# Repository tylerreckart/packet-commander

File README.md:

# Packet Commander
Complete 8-button WiFi IoT controller with hardware designs, firmware, and desktop configurator. Advanced configuration management, power optimization, and multi-protocol capabilities.

## Overview

Packet Commander is a complete IoT development platform featuring 8 programmable buttons with LED feedback, comprehensive WiFi connectivity, and intelligent power management. Includes hardware schematics, ESP32 firmware, and cross-platform Electron configurator for smart home automation, network testing, and custom IoT applications.

### Key Features
- **8 Programmable Buttons**: Directly supports HTTP and Webhook actions.
- **Smart Power Management**: Includes battery monitoring and optimized CPU frequency for power efficiency.
- **Desktop App**: Full-featured Electron configurator with device management.
- **Persistent Storage**: Configuration saved to flash memory on the device.
- **Multi-Protocol Support**: Firmware directly supports HTTP/HTTPS and Webhook.
- **Network Discovery**: Automatic device detection and configuration synchronization via the desktop application.

### Hardware Specs
- **MCU**: Arduino Nano ESP32 (Dual-core, 240MHz).
- **Inputs**: 8× illuminated tactile buttons (PB86).
- **Power**: 9V battery → 3.3V regulated (6-8 hour runtime).
- **Network**: 2.4GHz WiFi 802.11b/g/n.
- **Current**: 80-240mA.
- **Storage**: 4MB Flash, EEPROM for configuration.
- **Battery Monitor**: Real-time voltage sensing with low-battery alerts.

## Developer Quick Start

### For Configurator Development
```bash
# Install dependencies and run configurator
npm install
npm run build
npm run dev
```

### For Hardware Development
- Flash `firmware/patcom.cpp` to Arduino Nano ESP32
- Use configurator to connect and test device
- See [Circuit Assembly](#circuit-assembly) for complete build guide

### Prerequisites
- Node.js 18+ (for configurator)
- Arduino IDE 2.0+ (for firmware)
- KiCad (for hardware modifications)

## Quick Start

### 1. Hardware Setup
- Flash the firmware to your Arduino Nano ESP32.
- Connect 9V battery to power input.
- Power LED will indicate system status.

### 2. First Boot Configuration
1. Power on device - it will create "PATCOM-Config" WiFi hotspot.
2. Connect to hotspot (password: `patcom123`).
3. Open browser to `192.168.4.1`.
4. Configure your WiFi network and device settings.
5. Device will restart and connect to your network.

### 3. Desktop Configuration App

#### Development Commands
```bash
# Install dependencies
npm install

# Build all TypeScript
npm run build

# Run in development mode (with debug output)
npm run dev

# Run in production mode
npm start

# Build for distribution
npm run dist

# Type checking and linting
npm run type-check
npm run lint
```

#### Configurator Features
- **Device Auto-Detection**: USB serial and network discovery
- **Real-time Configuration**: Live button testing and LED control
- **Bulk Operations**: Configure multiple devices simultaneously
- **Configuration Backup**: Save/load device configurations as JSON
- **Debug Console**: Monitor device communication and troubleshoot issues

### 4. Device Discovery & Configuration
- Click "Discover Devices" to find controllers on your network
- Configure button actions: HTTP requests, webhooks.
- Upload configuration to device
- Test buttons and monitor activity

## Firmware Installation

### Arduino IDE Setup
- Download [Arduino IDE 2.0+](https://www.arduino.cc/en/software)
- Add ESP32 board URL in Preferences:
  ```
  https://espressif.github.io/arduino-esp32/package_esp32_index.json
  ```
- Install "Arduino ESP32 Boards" via Board Manager
- Install required libraries: ArduinoJson, AsyncUDP, ESPmDNS

### Firmware Upload
- Connect Arduino via USB-C
- Select: **Tools → Board → Arduino Nano ESP32**
- Select your port
- Open `firmware/patcom.cpp`
- Click Upload

## Configuration Management

### Button Action Types
- **HTTP/HTTPS**: Send GET/POST/PUT requests with custom headers and body
- **Webhook**: Secure webhook calls with device context and secrets
- **None**: Disable button (LED-only feedback)

### Device Settings
- **Network**: WiFi credentials, static IP configuration
- **Discovery**: Device name, auto-discovery, config sync settings
- **API Keys**: Secure storage for service credentials

### Configuration Storage
- Settings persisted to ESP32 flash memory
- Automatic backup during low battery
- Configuration hash verification
- Remote sync with desktop app

## Development & Debugging

### Device Communication
The configurator communicates with devices via:
- **USB Serial**: Direct connection for development (115200 baud)
- **Network Discovery**: UDP broadcast for deployed devices
- **HTTP API**: RESTful configuration on device port 80

### Debugging Tips
- Enable debug mode: `npm run dev` shows detailed console output
- Serial monitor: Built-in serial console for direct device communication
- Network scanner: "Discover Devices" shows all responsive controllers
- Configuration validation: Real-time validation with error highlighting

### File Structure
```
src/
├── main.ts              # Electron main process
├── preload.ts           # Secure IPC bridge  
├── renderer/            # UI components
├── services/            # Device communication
└── types/               # TypeScript definitions

firmware/
└── patcom.cpp           # ESP32 firmware

hardware/
└── *.kicad_*           # PCB design files
```

## Serial Commands (115200 baud)
- `STATUS` - Device information and battery status
- `CONFIG` - Display current configuration as JSON
- `SET_CONFIG:<json>` - Upload new configuration
- `TEST:<n>` - Test button n (0-7)
- `WIFI` - WiFi connection status
- `BATTERY` - Current battery voltage
- `HELP` - List all available commands

## Pin Connections

| Function | Pin | | Function | Pin |
|----------|-----|-|----------|-----|
| Button 0-7 | D2-D9 | | LED 0-7 | A0-A7 |
| Battery Monitor | A8 | | Status LED | D13 |
| Power In | 3V3 | | Ground | GND |
| USB Serial | USB-C | | Programming | BOOT + RESET |

## Circuit Assembly

### Parts List
- Packet Commander PCB
- Arduino Nano ESP32
- 8× PB86 switches
- RECOM R-78E3.3-1.0 regulator
- Capacitors: 100µF, 470µF, 10µF
- Resistors: 100kΩ, 33kΩ, 1kΩ
- 9V battery connector
- Terminal blocks

### Wiring
1. Battery → Regulator → Arduino 3V3 pin
2. Each button: terminal → Arduino pin, LED+ → analog pin
3. All grounds connected together
4. Battery monitor: voltage divider to D12

## Example Use Cases

### Smart Home Control
```json
{
  "action": "http",
  "config": {
    "url": "http://homeassistant.local:8123/api/services/light/toggle",
    "method": "POST",
    "headers": {"Authorization": "Bearer YOUR_TOKEN"},
    "body": "{\"entity_id\": \"light.living_room\"}"
  }
}
```

### Custom Webhook
```json
{
  "action": "webhook",
  "config": {
    "url": "https://api.example.com/webhook",
    "secret": "your-webhook-secret"
  }
}
```

## Troubleshooting

### Hardware Issues
| Issue | Solution |
|-------|----------|
| Upload fails | Hold RESET button during upload. Short GPIO0 to GND to reset the boot state. |
| No WiFi connection | Check 2.4GHz network, verify credentials |
| Short battery life | Normal: 6-8 hours, enable power saving |
| LEDs dim/flickering | Low battery or loose connections |
| Configuration not saving | Check flash memory, try factory reset |

### Configurator Issues  
| Issue | Solution |
|-------|----------|
| **Configurator won't start** | Run `npm run clean && npm install && npm run build` |
| **Device not detected** | Check USB drivers, try different cable, verify 115200 baud |
| **Network discovery fails** | Disable firewall, ensure same subnet, check UDP port 12345 |
| **Configuration upload fails** | Verify device connection, check JSON syntax, try smaller config |
| **Build errors** | Update Node.js to 18+, clear node_modules, reinstall |
| **TypeScript errors** | Run `npm run type-check` for detailed diagnostics |

## License

MIT License - Open source hardware and software.

## Contributing

Packet Commander is open source hardware and software. Contributions welcome for hardware, firmware, or configurator!

### Development Areas
- **Hardware**: PCB improvements, new form factors (`/hardware`)
- **Firmware**: ESP32 code, new protocols (`/firmware`) 
- **Configurator**: Electron app features (`/src`)

### Process
1. Fork the repository
2. Create a feature branch
3. Test with hardware if possible
4. Submit a pull request with detailed description

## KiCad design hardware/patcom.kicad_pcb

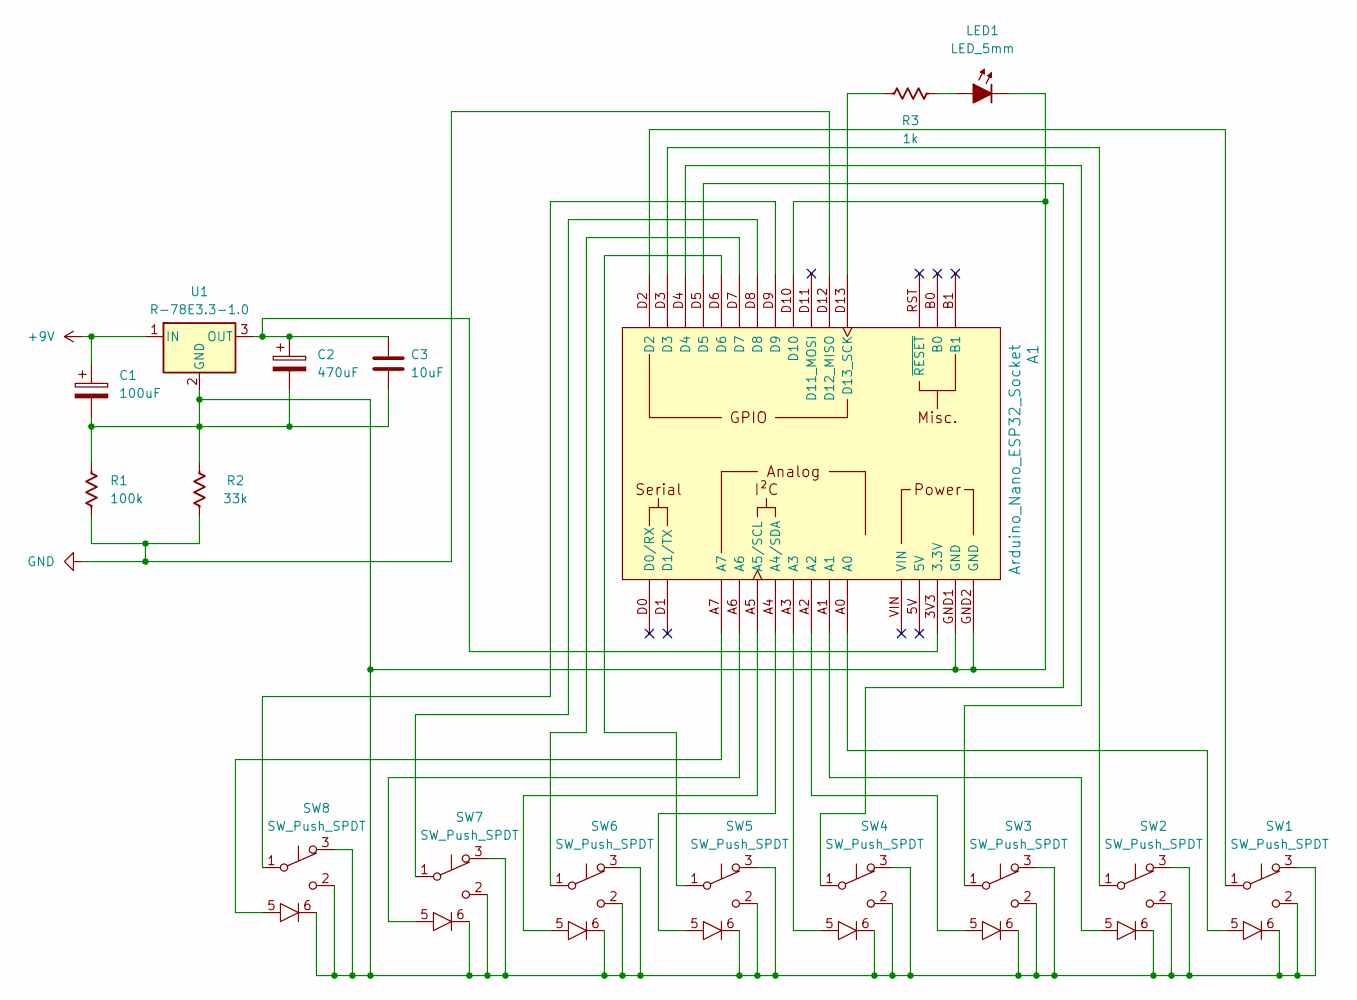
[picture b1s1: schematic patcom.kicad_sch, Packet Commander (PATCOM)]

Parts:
A1: Arduino_Nano_ESP32_Socket
C1: 100uF; CP_Radial_D5.0mm_P2.00mm
C2: 470uF; CP_Radial_D10.0mm_P5.00mm
C3: 10uF; C_Disc_D5.0mm_W2.5mm_P5.00mm
LED1: LED_5mm; LED_D5.0mm
R1: 100k; R_Axial_DIN0207_L6.3mm_D2.5mm_P10.16mm_Horizontal
R2: 33k; R_Axial_DIN0207_L6.3mm_D2.5mm_P10.16mm_Horizontal
R3: 1k; R_Axial_DIN0207_L6.3mm_D2.5mm_P10.16mm_Horizontal
SW1, SW2, SW3, SW4, SW5, SW6, SW7, SW8: SW_Push_SPDT; PB_86_A1
U1: R-78E3.3-1.0; Converter_DCDC_RECOM_R-78E-0.5_THT

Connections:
+9V: C1.1, U1.1 (IN); also elsewhere on the board
unnamed: A1.3V3 (3.3V), C2.1, C3.2, U1.3 (OUT)
unnamed: A1.A4 (A4/SDA), SW5.5 (LED+)
unnamed: A1.A5 (A5/SCL), SW6.5 (LED+)
unnamed: A1.D13 (D13_SCK), R3.2
unnamed: LED1.2 (A), R3.1
unnamed: A1.D2, SW1.1 (B)
unnamed: A1.A0, SW1.5 (LED+)
unnamed: A1.D3, SW2.1 (B)
unnamed: A1.A1, SW2.5 (LED+)
unnamed: A1.D4, SW3.1 (B)
unnamed: A1.A2, SW3.5 (LED+)
unnamed: A1.D5, SW4.1 (B)
unnamed: A1.A3, SW4.5 (LED+)
unnamed: A1.D6, SW5.1 (B)
unnamed: A1.D7, SW6.1 (B)
unnamed: A1.D8, SW7.1 (B)
unnamed: A1.A6, SW7.5 (LED+)
unnamed: A1.D9, SW8.1 (B)
unnamed: A1.A7, SW8.5 (LED+)

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
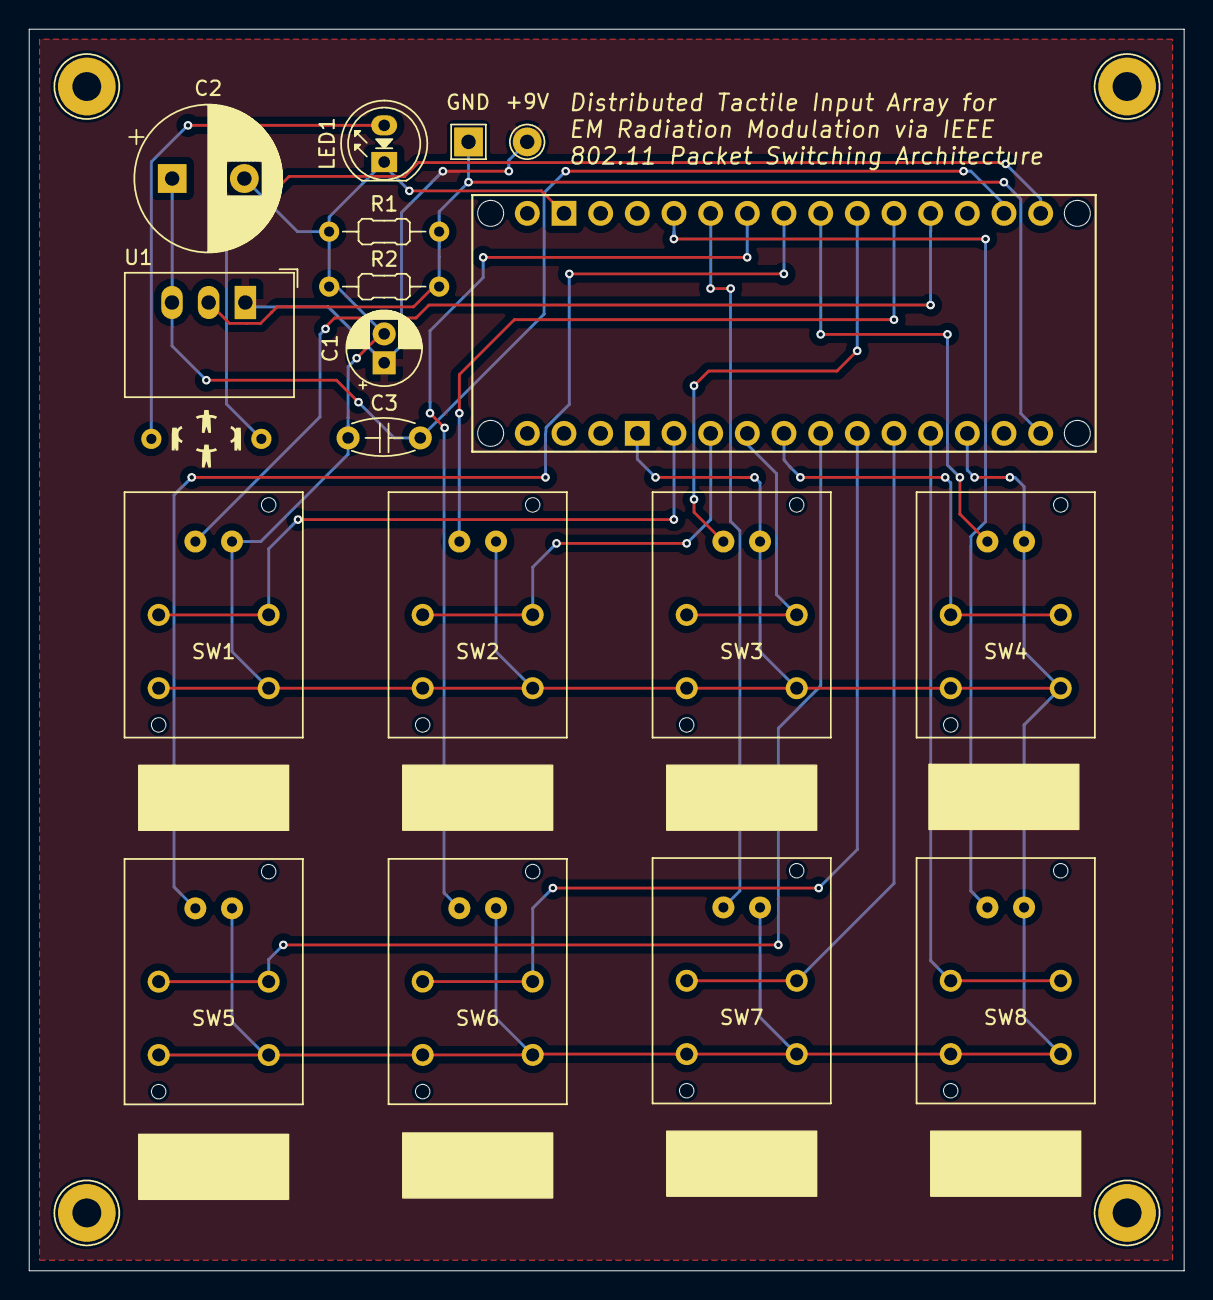
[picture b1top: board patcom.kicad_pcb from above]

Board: 2 copper layers, 80.0 x 86.0 mm, 19 parts (0 on the bottom side), 22 nets.

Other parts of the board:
+9V: TestPoint_THTPad_D2.0mm_Drill1.0mm
GND: TestPoint_THTPad_2.0x2.0mm_Drill1.0mm

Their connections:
+9V: +9V.1; also elsewhere on the board

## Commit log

2025-07-24 initialize repository
2025-07-25 update pcb
2025-07-31 basic configurator
2025-08-02 clean up desktop app
2025-08-04 improve configurator network settings
2025-08-04 clean up
2025-08-04 better configuration mapping
2025-08-05 further work on configurator
2025-08-05 fix singing issues
2025-08-05 improve render conditions
